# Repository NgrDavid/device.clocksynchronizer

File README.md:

## Harp Clock Synchronizer ##

Outputs clock synchronization for up to 6 Harp devices when in "Generator" mode. If there is a need to synchronize more devices, the device can be set to "Repeater" mode and receive a master clock signal from another Clock Synchronizer device set to "Generator" mode.

### Key Features ###

* Can be used as a Generator (up to 6 devices) or Repeater.
* Synchronization error: ± 42 µS

### Connectivity ###

* 1x clock sync input (CLKIN) [stereo jack]
* 1x USB (for power) [USB type B]
* 6x clock sync output (CLKOUT1 to CLKOUT6) [stereo jack]

## Interface ##

The interface with the Harp board can be done through [Bonsai](https://bonsai-rx.org/).

## Licensing ##

Each subdirectory will contain a license or, possibly, a set of licenses if it involves both hardware and software.

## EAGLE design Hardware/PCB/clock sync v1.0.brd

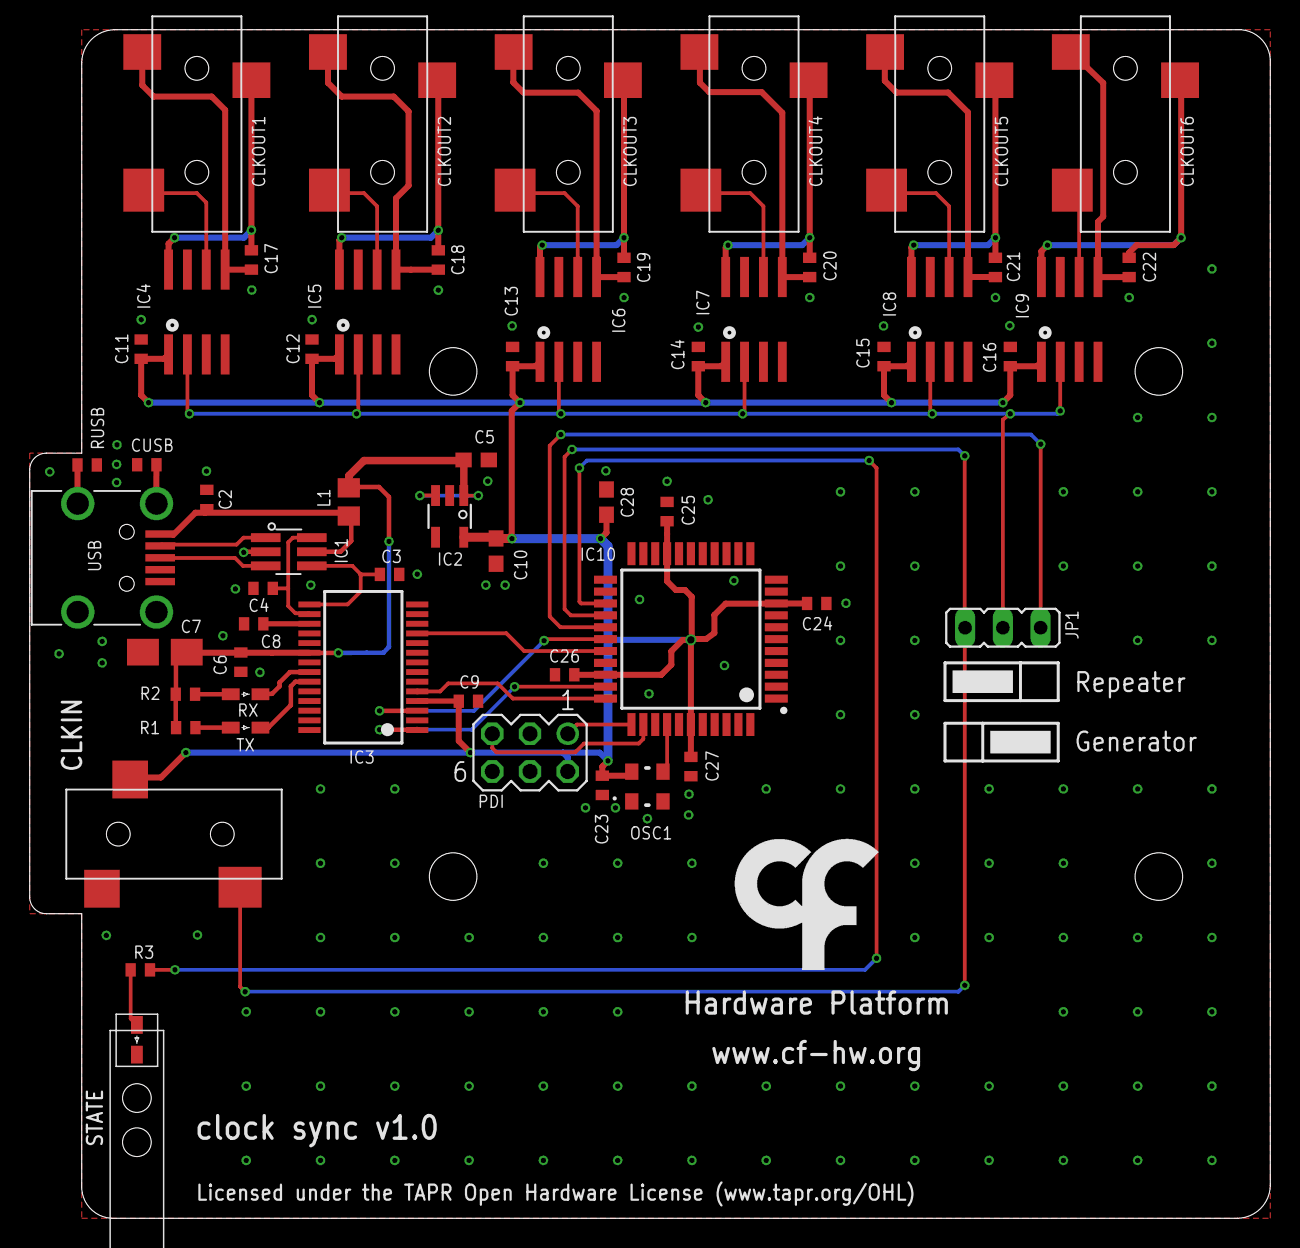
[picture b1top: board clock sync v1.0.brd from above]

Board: 2 copper layers, 83.5 x 80.0 mm, 59 parts (0 on the bottom side), 45 nets.

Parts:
C2, C6, C8, C9, C11, C12, C13, C14, C15, C16, C17, C18, C19, C20, C21, C22, C23, C24, C25, C26: 100nF; C0402
C3, C4: 47pF; C0402
C5, C10, C28: 10uF; C0603
C7: 4.7uF; A/3216-18W
C27: 330nF; C0402
CLKIN: 35RASMT2BHNTRX
CLKOUT1, CLKOUT2, CLKOUT3, CLKOUT4, CLKOUT5, CLKOUT6: 35RASMT2BHNTRX
CUSB: 4.7nF; C0402
IC1: USBLC6-2SC6; SOT23-6L
IC2: LP5907MFX-3.3; TSOT23-5
IC3: FT232RL; SSOP28
IC4, IC5, IC6, IC7, IC8, IC9: SI8610; SO-08
IC10: ATXMEGAxxxA4U-AU; QFP80P1200X1200X120-44N
JP1: JP2_NO_NUMBERS
L1: ???; R0805
OSC1: OSCILLATOR_3.2X2.5
PDI: MA03-2
R1: 2050 NA; R0402
R2: 680 NA; R0402
R3: 68; R0402
RUSB: 1M; R0402
RX: GREEN NA; LED_HAND
STATE: GREEN; LED_HAND
TX: RED NA; LED_HAND
U$1: LED_PIPE_7513D2-L
U$9: LOGO_6
USB: 240-0002-1

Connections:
+5V: C5.1, C6.1, C7.+, IC2.1, IC2.3, IC3.20, L1.1, R1.2, R2.2
CLKOUT: IC4.2, IC5.2, IC6.2, IC7.2, IC8.2, IC9.2, JP1.2
CLK_IN: CLKIN.4, IC10.26, JP1.1
CLK_SYNC_OUT: IC10.27, JP1.3
FT_CTS: IC3.11, IC10.29
FT_RTS: IC3.3, IC10.28
FT_RXD: IC3.5, IC10.33
FT_TXD: IC3.1, IC10.32
GND: C2.2, C3.2, C4.2, C5.2, C6.2, C7.-, C8.2, C9.2, C10.2, C11.2, C12.2, C13.2, C14.2, C15.2, C16.2, C23.2, C24.2, C25.2, C26.2, C27.2, C28.2, CLKIN.5, CUSB.2, IC1.P$2, IC2.2, IC3.7, IC3.18, IC3.21, IC3.25, IC3.26, IC4.4, IC5.4, IC6.4, IC7.4, IC8.4, IC9.4, IC10.8, IC10.18, IC10.30, IC10.38, OSC1.P$2, PDI.6, RUSB.2, STATE.K, USB.P$5
unnamed: CLKOUT1.4, IC4.6
unnamed: C18.1, CLKOUT2.1, IC5.8
unnamed: C18.2, CLKOUT2.5, IC5.5
unnamed: CLKOUT2.4, IC5.6
unnamed: C19.1, CLKOUT3.1, IC6.8
unnamed: C19.2, CLKOUT3.5, IC6.5
unnamed: CLKOUT3.4, IC6.6
unnamed: C20.1, CLKOUT4.1, IC7.8
unnamed: C20.2, CLKOUT4.5, IC7.5
unnamed: CLKOUT4.4, IC7.6
unnamed: C21.1, CLKOUT5.1, IC8.8
unnamed: C21.2, CLKOUT5.5, IC8.5
unnamed: C17.1, CLKOUT1.1, IC4.8
unnamed: CLKOUT5.4, IC8.6
unnamed: C22.1, CLKOUT6.1, IC9.8
unnamed: C22.2, CLKOUT6.5, IC9.5
unnamed: C17.2, CLKOUT1.5, IC4.5
unnamed: CLKOUT6.4, IC9.6
unnamed: R3.1, STATE.A
unnamed: C8.1, IC3.17
unnamed: C2.1, IC1.P$5, L1.2, USB.P$1
unnamed: IC1.P$1, USB.P$2
unnamed: R2.1, RX.A
unnamed: IC3.23, TX.K
unnamed: IC3.22, RX.K
unnamed: IC1.P$3, USB.P$3
unnamed: CUSB.1, USB.SHIELD_4
unnamed: RUSB.1, USB.SHIELD_1
unnamed: R1.1, TX.A
OSC1: IC10.37, OSC1.P$3
PDI-CLK: IC10.35, PDI.5
PDI-DATA: IC10.34, PDI.1
STATE: IC10.25, R3.2
USBDM: C4.1, IC1.P$6, IC3.16
USBDP: C3.1, IC1.P$4, IC3.15
VCCIO: C9.1, C10.1, C11.1, C12.1, C13.1, C14.1, C15.1, C16.1, C23.1, C24.1, C25.1, C26.1, C27.1, C28.1, CLKIN.1, IC2.5, IC3.4, IC4.1, IC5.1, IC6.1, IC7.1, IC8.1, IC9.1, IC10.9, IC10.19, IC10.31, IC10.39, OSC1.P$4, PDI.2

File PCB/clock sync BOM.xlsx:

Board | Part(s) | Quantity | Description | Distributor | Part. No.
 | IC1 | 1 | ESD Protection Low Cap | Mouser | 511-USBLC6-2SC6
 | IC2 | 1 | LDO 250mA Ultra-Lo Noise LDO Reg | Mouser | 595-LP5907MFX-3.3NPB
 | IC3 | 1 | IC USB USB to Serial UART Enhanced IC SSOP-28 | Mouser | 895-FT232RL
 | IC4, IC5, IC6, IC7, IC8, IC9 | 6 | Isoladores digitais Single Ch 3.75kV Iso 150M 1/0, def out=LO | Mouser | 634-SI8610BC-B-IS
 | IC10 | 1 | ATXMEGA64A4U-AU, ATxmega, 32 MHz, 64 KB, 4 KB, 44, TQFP | Mouser | 556-ATXMEGA64A4U-AU
 | C3, C4 | 2 | CAP CER 47pF 50V ±5% C0G 0402 | Mouser | 77-VJ0402A470JXACBC
 | CUSB | 1 | CAP CER 4.7nF 100V ±10% X7R 0402 | Mouser | 81-GRM155R72A472KA01
 | C2, C6, C8, C9, C11, C12, C13, C14, C15, C16, C17, C18, C19, C20, C21, C22, C23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 | 20 | CAP CER 100nF 10V X5R 0402 | REEL | REEL
 | C27 | 1 | CAP CER 0.33uF 10V ±10% X5R 0402 | Mouser | GRM155R61A334KE15D
 | C7 | 1 | CAP TAN 4.7uF 6.3V ±10% 1206 | Mouser | 80-T491A475K006
 | C5, C10, C28 | 3 | CAP CER 10uF 10V ±10% X5R 0603 | Mouser | 81-GRM188R61A106KE9D
 | R3 | 1 | RES SMD 68Ω OHM 5% 0402 | Mouser | 71-CRCW0402-68-E3
 | RUSB | 1 | RES SMD 1MΩ 1% 0402 | Mouser | 652-CR0402FX-1004GLF
 | L1 | 1 | 40ohms 100MHz 1.5A Monolithic 0805 SMD | Mouser | 875-MI0805K400R-10
 | STATE | 1 | LED, Green, 1.6mm x 0.8mm, 566 nm, 2.1 V, 20 mA, 15 mcd | Mouser | 78-TLMP1100-GS08
 | OSC1 | 1 | 32MHz 10ppm | Mouser | 998-1001CI5032.0000T
 | PDI | 1 | 6P DR UNSHRD HRD | Mouser | 649-67996-206HLF
 | JP1 | 1 | 3POS Gold Male | Mouser | 649-68001-203HLF
 |  | 1 | SHUNT JUMPER, 2POS | Farnell | 2396301
 | USB | 1 | UX60-MB-5S8 | Mouser | 798-UX60-MB-5S8
 | USB Cable | 1 | USB A - MINI-B 0.8M - MINI-B 0.8M BLACK | Mouser | 538-88732-8502
 | CLKIN, CLKOUT1-6 | 7 | SMT 3.5 STEREO REEL | Mouser | 502-35RASMT2BHNTRX
 |  | 1 | Tubos de Luz LED CML LIGHTPIPE | Mouser | 606-7513D2-L
 |  | 5 | 3.5mm Stereo Jack Plug, 3.5mm Stereo Jack Plug, 3.9 ft, 1.2 m, Black | Farnell | 3712278
 |  | 1 | 3.5mm Stereo Jack Plug, 3.5mm Stereo Jack Plug, 16 ft, 5 m, Black | Farnell | 3712527
 | Components | 62
 | Licensed under the TAPR Open Hardware License (www.tapr.org/OHL)
 | Copyright 2017 Artur Silva and Filipe Carvalho

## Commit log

2017-04-21 Added entire files set.
2017-04-28 Updated to Harp 0.11.
2017-04-28 Added the PCB files.
2017-04-28 Updated Atmel's project.
2017-04-28 Updated to firmware version 1.1.
2017-05-31 Updated to Harp version 0.16.
2017-05-31 Returned to firmware version 1.0.
2018-01-11 Updated to Atxmega Harp core version 1.1.
2018-01-11 Fixed the firmware version.
2018-01-30 Updated to Atxmega Harp core version 1.3.
2022-12-17 Rename files
2022-12-17 Add licenses and readme
2022-12-17 Renamed files
2022-12-23 refactor repository structure
2023-04-11 Fix README.md header
2023-08-18 Update README file
2023-08-18 Add device schema
2023-08-18 Add generated device interface
2023-08-19 remove file extensions
2023-08-20 Update PCB image asset
2023-08-20 Add Firmware .gitignore
2023-08-20 Remove license files externsions
2023-08-20 Add Hardware .gitignore
2023-08-20 Add Mechanical folder and license
2023-08-22 Update start core parameters
2023-08-22 Update comment description
2023-08-23 Update .cppproj library path
2024-11-13 Update device schema source
2024-11-13 Update package metadata, version and add library package
2024-11-13 Update generators and regenerate interface
2025-05-16 Create basic CI/CD for interface package
